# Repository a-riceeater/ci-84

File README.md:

# ci-84: California Instruments 84
An open source, ti-84 equivalent graphing calculator. 

This repository contains CAD files, KiCad project files, and firmware for the calculator.

## Hardware Specifications

- As of 3/5/25, the microcontroller will be a [STM32L471RGT6TR](https://www.digikey.com/en/products/detail/stmicroelectronics/STM32L471RGT6TR/8257935)

- Floating point math

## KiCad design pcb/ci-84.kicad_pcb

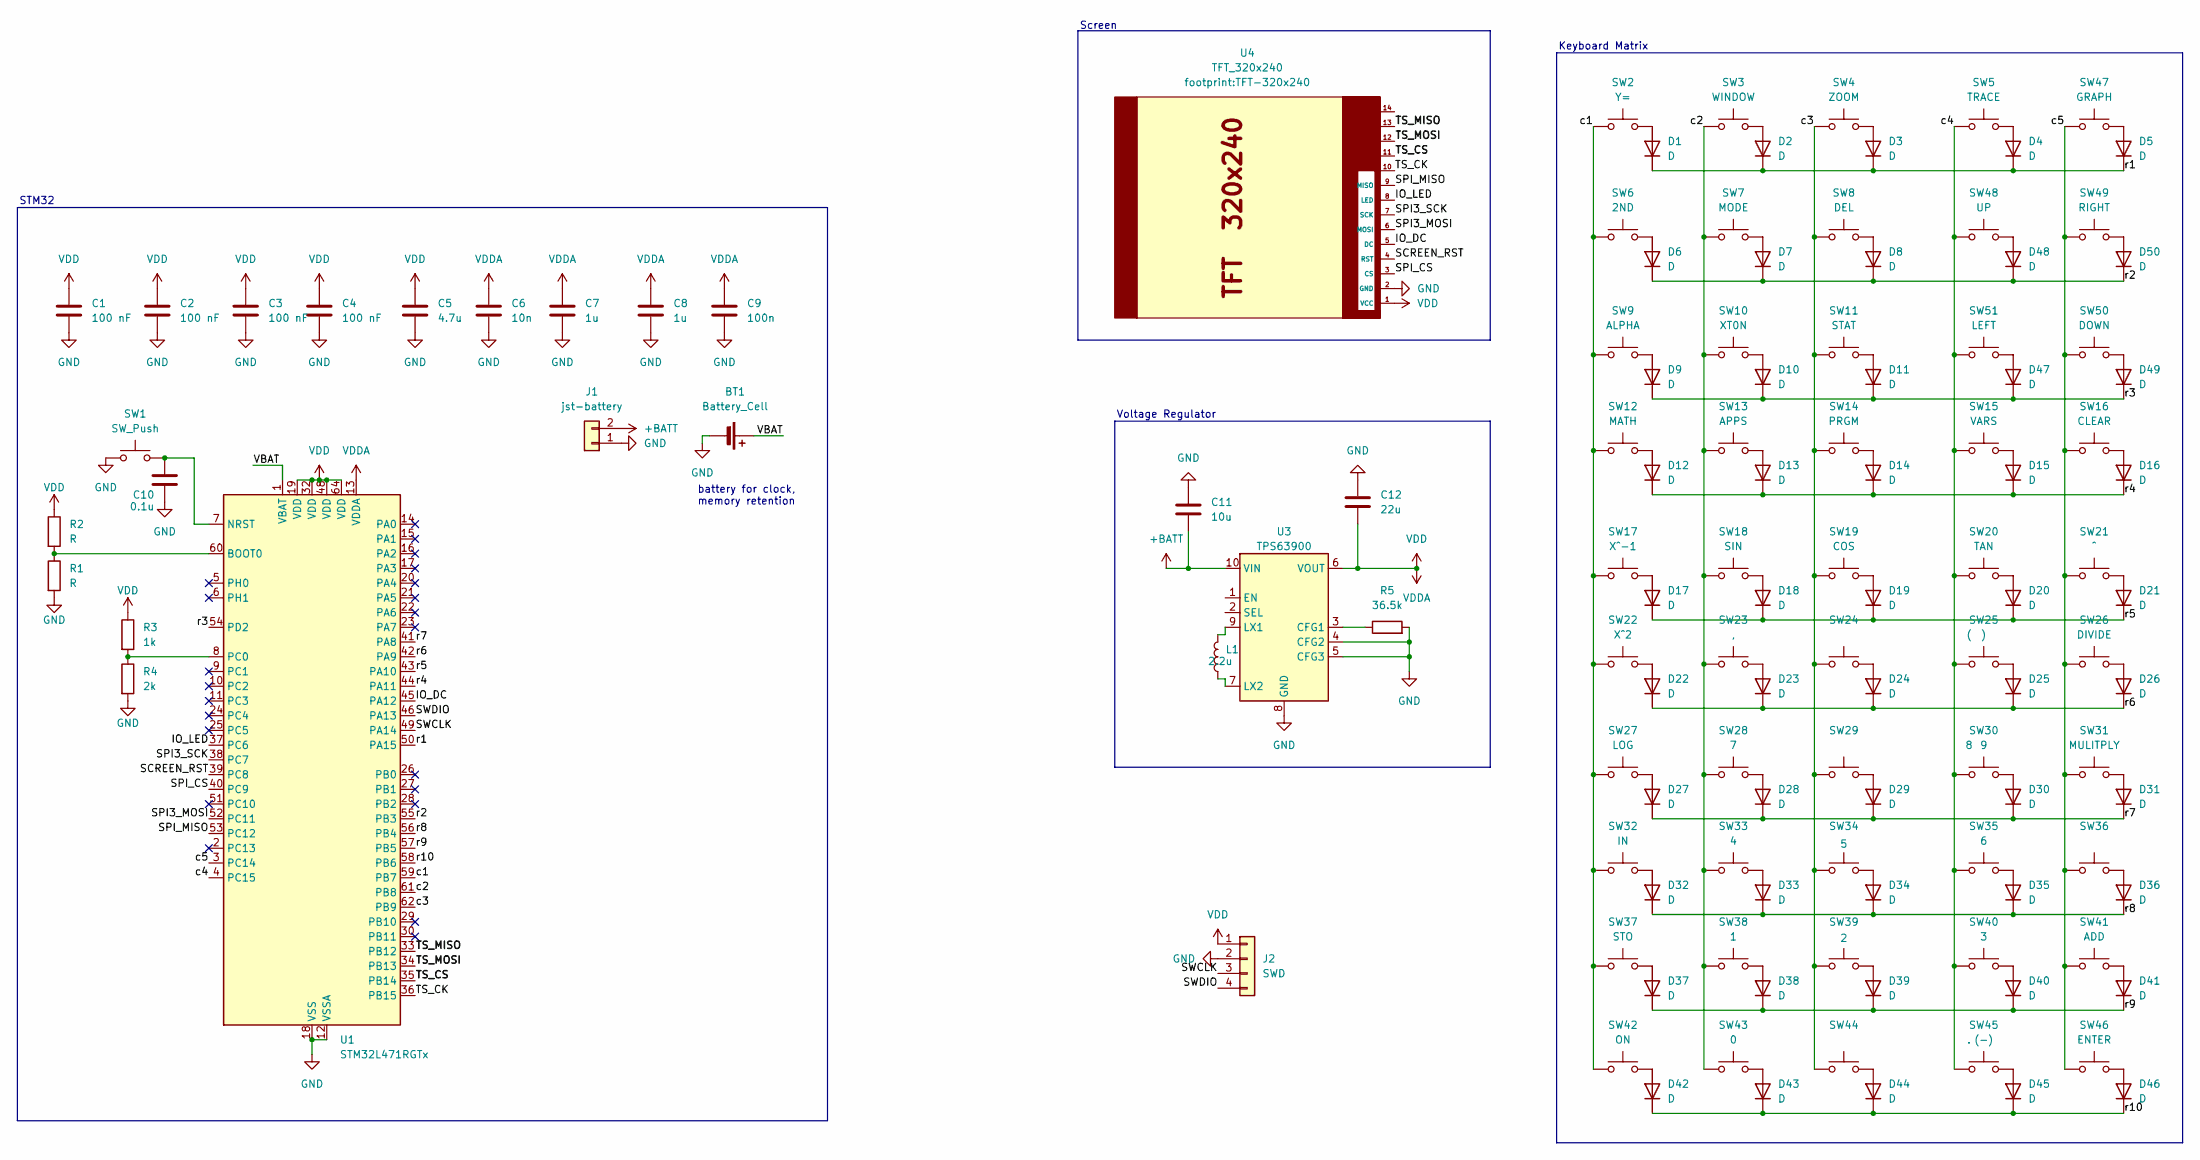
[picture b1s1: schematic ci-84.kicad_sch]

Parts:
BT1: Battery_Cell; BatteryHolder_MPD_BC2003_1x2032
C1, C2, C3, C4: 100 nF; C_0603_1608Metric
C5: 4.7u; C_0603_1608Metric
C6: 10n; C_0603_1608Metric
C7, C8: 1u; C_0603_1608Metric
C9: 100n; C_0603_1608Metric
C10: 0.1u; C_0603_1608Metric
C11: 10u; C_0805_2012Metric
C12: 22u; C_1206_3216Metric
D1, D2, D3, D4, D5, D6, D7, D8, D9, D10, D11, D12, D13, D14, D15, D16, D17, D18, D19, D20, D21, D22, D23, D24, D25, D26, D27, D28, D29, D30, D31, D32, D33, D34, D35, D36, D37, D38, D39, D40, D41, D42, D43, D44, D45, D46, D47, D48, D49, D50: D; D_SOD-123
J1: jst-battery; JST_PH_B2B-PH-K_1x02_P2.00mm_Vertical
J2: SWD; PinHeader_1x04_P2.54mm_Vertical
L1: 2.2u; L_1008_2520Metric
R1, R2: R; R_0603_1608Metric
R3: 1k; R_0603_1608Metric
R4: 2k; R_0603_1608Metric
R5: 36.5k; R_0603_1608Metric
SW1: SW_Push; SW4_1825910-B_TEC
SW2: Y=; SW_Tactile_SPST_NO_Straight_CK_PTS636Sx25SMTRLFS
SW3: WINDOW; SW_Tactile_SPST_NO_Straight_CK_PTS636Sx25SMTRLFS
SW4: ZOOM; SW_Tactile_SPST_NO_Straight_CK_PTS636Sx25SMTRLFS
SW5: TRACE; SW_Tactile_SPST_NO_Straight_CK_PTS636Sx25SMTRLFS
SW6: 2ND; SW_Tactile_SPST_NO_Straight_CK_PTS636Sx25SMTRLFS
SW7: MODE; SW_Tactile_SPST_NO_Straight_CK_PTS636Sx25SMTRLFS
SW8: DEL; SW_Tactile_SPST_NO_Straight_CK_PTS636Sx25SMTRLFS
SW9: ALPHA; SW_Tactile_SPST_NO_Straight_CK_PTS636Sx25SMTRLFS
SW10: XT0N; SW_Tactile_SPST_NO_Straight_CK_PTS636Sx25SMTRLFS
SW11: STAT; SW_Tactile_SPST_NO_Straight_CK_PTS636Sx25SMTRLFS
SW12: MATH; SW_Tactile_SPST_NO_Straight_CK_PTS636Sx25SMTRLFS
SW13: APPS; SW_Tactile_SPST_NO_Straight_CK_PTS636Sx25SMTRLFS
SW14: PRGM; SW_Tactile_SPST_NO_Straight_CK_PTS636Sx25SMTRLFS
SW15: VARS; SW_Tactile_SPST_NO_Straight_CK_PTS636Sx25SMTRLFS
SW16: CLEAR; SW_Tactile_SPST_NO_Straight_CK_PTS636Sx25SMTRLFS
SW17: X^-1; SW_Tactile_SPST_NO_Straight_CK_PTS636Sx25SMTRLFS
SW18: SIN; SW_Tactile_SPST_NO_Straight_CK_PTS636Sx25SMTRLFS
SW19: COS; SW_Tactile_SPST_NO_Straight_CK_PTS636Sx25SMTRLFS
SW20: TAN; SW_Tactile_SPST_NO_Straight_CK_PTS636Sx25SMTRLFS
SW21: ^; SW_Tactile_SPST_NO_Straight_CK_PTS636Sx25SMTRLFS
SW22: X^2; SW_Tactile_SPST_NO_Straight_CK_PTS636Sx25SMTRLFS
SW23: ,; SW_Tactile_SPST_NO_Straight_CK_PTS636Sx25SMTRLFS
SW24: (; SW_Tactile_SPST_NO_Straight_CK_PTS636Sx25SMTRLFS
SW25: ); SW_Tactile_SPST_NO_Straight_CK_PTS636Sx25SMTRLFS
SW26: DIVIDE; SW_Tactile_SPST_NO_Straight_CK_PTS636Sx25SMTRLFS
SW27: LOG; SW_Tactile_SPST_NO_Straight_CK_PTS636Sx25SMTRLFS
SW28: 7; SW_Tactile_SPST_NO_Straight_CK_PTS636Sx25SMTRLFS
SW29: 8; SW_Tactile_SPST_NO_Straight_CK_PTS636Sx25SMTRLFS
SW30: 9; SW_Tactile_SPST_NO_Straight_CK_PTS636Sx25SMTRLFS
SW31: MULITPLY; SW_Tactile_SPST_NO_Straight_CK_PTS636Sx25SMTRLFS
SW32: IN; SW_Tactile_SPST_NO_Straight_CK_PTS636Sx25SMTRLFS
SW33: 4; SW_Tactile_SPST_NO_Straight_CK_PTS636Sx25SMTRLFS
SW34: 5; SW_Tactile_SPST_NO_Straight_CK_PTS636Sx25SMTRLFS
SW35: 6; SW_Tactile_SPST_NO_Straight_CK_PTS636Sx25SMTRLFS
SW36: SUBTRACT; SW_Tactile_SPST_NO_Straight_CK_PTS636Sx25SMTRLFS
SW37: STO; SW_Tactile_SPST_NO_Straight_CK_PTS636Sx25SMTRLFS
SW38: 1; SW_Tactile_SPST_NO_Straight_CK_PTS636Sx25SMTRLFS
SW39: 2; SW_Tactile_SPST_NO_Straight_CK_PTS636Sx25SMTRLFS
SW40: 3; SW_Tactile_SPST_NO_Straight_CK_PTS636Sx25SMTRLFS
SW41: ADD; SW_Tactile_SPST_NO_Straight_CK_PTS636Sx25SMTRLFS
SW42: ON; SW_Tactile_SPST_NO_Straight_CK_PTS636Sx25SMTRLFS
SW43: 0; SW_Tactile_SPST_NO_Straight_CK_PTS636Sx25SMTRLFS
SW44: .; SW_Tactile_SPST_NO_Straight_CK_PTS636Sx25SMTRLFS
SW45: (-); SW_Tactile_SPST_NO_Straight_CK_PTS636Sx25SMTRLFS
SW46: ENTER; SW_Tactile_SPST_NO_Straight_CK_PTS636Sx25SMTRLFS
SW47: GRAPH; SW_Tactile_SPST_NO_Straight_CK_PTS636Sx25SMTRLFS
SW48: UP; SW_Tactile_SPST_NO_Straight_CK_PTS636Sx25SMTRLFS
SW49: RIGHT; SW_Tactile_SPST_NO_Straight_CK_PTS636Sx25SMTRLFS
SW50: DOWN; SW_Tactile_SPST_NO_Straight_CK_PTS636Sx25SMTRLFS
SW51: LEFT; SW_Tactile_SPST_NO_Straight_CK_PTS636Sx25SMTRLFS
U1: STM32L471RGTx; LQFP-64_10x10mm_P0.5mm
U3: TPS63900; WSON-10-1EP_2.5x2.5mm_P0.5mm_EP1.2x2mm_ThermalVias
U4: TFT_320x240; TFT-320x240

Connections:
+BATT: C11.2, J1.2, U3.10 (VIN)
/IO_DC: U1.45 (PA12), U4.5 (DC)
/IO_LED: U1.37 (PC6), U4.8 (LED)
/SCREEN_RST: U1.39 (PC8), U4.4 (RST)
/SPI3_MOSI: U1.52 (PC11), U4.6 (MOSI)
/SPI3_SCK: U1.38 (PC7), U4.7 (SCK)
/SPI_CS: U1.40 (PC9), U4.3 (CS)
/SPI_MISO: U1.53 (PC12), U4.9 (MISO)
/SWCLK: J2.3, U1.49 (PA14)
/SWDIO: J2.4, U1.46 (PA13)
/TS_CK: U1.36 (PB15), U4.10
/TS_CS: U1.35 (PB14), U4.11
/TS_MISO: U1.33 (PB12), U4.13
/TS_MOSI: U1.34 (PB13), U4.12
/VBAT: BT1.1 (+), U1.1 (VBAT)
/c1: SW2.1, SW6.2, SW9.2, SW12.2, SW17.2, SW22.2, SW27.2, SW32.2, SW37.2, SW42.2, U1.59 (PB7)
/c2: SW3.2, SW7.2, SW10.2, SW13.2, SW18.2, SW23.2, SW28.2, SW33.2, SW38.2, SW43.2, U1.61 (PB8)
/c3: SW4.2, SW8.2, SW11.2, SW14.2, SW19.2, SW24.2, SW29.2, SW34.2, SW39.2, SW44.2, U1.62 (PB9)
/c4: SW5.2, SW15.2, SW20.2, SW25.2, SW30.2, SW35.2, SW40.2, SW45.2, SW48.2, SW51.2, U1.4 (PC15)
/c5: SW16.2, SW21.2, SW26.2, SW31.2, SW36.2, SW41.2, SW46.2, SW47.2, SW49.2, SW50.2, U1.3 (PC14)
/r1: D1.1 (K), D2.1 (K), D3.1 (K), D4.1 (K), D5.1 (K), U1.50 (PA15)
/r2: D6.1 (K), D7.1 (K), D8.1 (K), D48.1 (K), D50.1 (K), U1.55 (PB3)
/r3: D9.1 (K), D10.1 (K), D11.1 (K), D47.1 (K), D49.1 (K), U1.54 (PD2)
/r4: D12.1 (K), D13.1 (K), D14.1 (K), D15.1 (K), D16.1 (K), U1.44 (PA11)
/r5: D17.1 (K), D18.1 (K), D19.1 (K), D20.1 (K), D21.1 (K), U1.43 (PA10)
/r6: D22.1 (K), D23.1 (K), D24.1 (K), D25.1 (K), D26.1 (K), U1.42 (PA9)
/r7: D27.1 (K), D28.1 (K), D29.1 (K), D30.1 (K), D31.1 (K), U1.41 (PA8)
/r8: D32.1 (K), D33.1 (K), D34.1 (K), D35.1 (K), D36.1 (K), U1.56 (PB4)
/r9: D37.1 (K), D38.1 (K), D39.1 (K), D40.1 (K), D41.1 (K), U1.57 (PB5)
/r10: D42.1 (K), D43.1 (K), D44.1 (K), D45.1 (K), D46.1 (K), U1.58 (PB6)
GND: BT1.2 (-), C1.2, C2.2, C3.2, C4.2, C5.2, C6.2, C7.2, C8.2, C9.2, C10.2, C11.1, C12.1, J1.1, J2.2, R1.2, R4.2, R5.2, SW1.1, U1.12 (VSSA), U1.18 (VSS), U1.31 (VSS), U1.47 (VSS), U1.63 (VSS), U3.4 (CFG2), U3.5 (CFG3), U3.8 (GND), U3.11 (GND), U4.2 (GND)
unnamed: D1.2 (A), SW2.2
unnamed: D2.2 (A), SW3.1
unnamed: D3.2 (A), SW4.1
unnamed: D4.2 (A), SW5.1
unnamed: D5.2 (A), SW47.1
unnamed: D6.2 (A), SW6.1
unnamed: D7.2 (A), SW7.1
unnamed: D8.2 (A), SW8.1
unnamed: D9.2 (A), SW9.1
unnamed: D10.2 (A), SW10.1
unnamed: D11.2 (A), SW11.1
unnamed: D12.2 (A), SW12.1
unnamed: D13.2 (A), SW13.1
unnamed: D14.2 (A), SW14.1
unnamed: D15.2 (A), SW15.1
unnamed: D16.2 (A), SW16.1
unnamed: D17.2 (A), SW17.1
unnamed: D18.2 (A), SW18.1
unnamed: D19.2 (A), SW19.1
unnamed: D20.2 (A), SW20.1
unnamed: D21.2 (A), SW21.1
unnamed: D22.2 (A), SW22.1
unnamed: D23.2 (A), SW23.1
unnamed: D24.2 (A), SW24.1
unnamed: D25.2 (A), SW25.1
unnamed: D26.2 (A), SW26.1
unnamed: D27.2 (A), SW27.1
unnamed: D28.2 (A), SW28.1
unnamed: D29.2 (A), SW29.1
unnamed: D30.2 (A), SW30.1
unnamed: D31.2 (A), SW31.1
unnamed: D32.2 (A), SW32.1
unnamed: D33.2 (A), SW33.1
unnamed: D34.2 (A), SW34.1
unnamed: D35.2 (A), SW35.1
unnamed: D36.2 (A), SW36.1
unnamed: D37.2 (A), SW37.1
unnamed: D38.2 (A), SW38.1
unnamed: D39.2 (A), SW39.1
unnamed: D40.2 (A), SW40.1
unnamed: D41.2 (A), SW41.1
unnamed: D42.2 (A), SW42.1
unnamed: D43.2 (A), SW43.1
unnamed: D44.2 (A), SW44.1
unnamed: D45.2 (A), SW45.1
unnamed: D46.2 (A), SW46.1
unnamed: D47.2 (A), SW51.1
unnamed: D48.2 (A), SW48.1
unnamed: D49.2 (A), SW50.1
unnamed: D50.2 (A), SW49.1
unnamed: R1.1, R2.2, U1.60 (BOOT0)
unnamed: C10.1, SW1.2, U1.7 (NRST)
unnamed: R3.2, R4.1, U1.8 (PC0)
unnamed: R5.1, U3.3 (CFG1)
unnamed: L1.2, U3.9 (LX1)
unnamed: L1.1, U3.7 (LX2)
VDD: C1.1, C2.1, C3.1, C4.1, C5.1, C6.1, C7.1, C8.1, C9.1, C12.2, J2.1, R2.1, R3.1, U1.13 (VDDA), U1.19 (VDD), U1.32 (VDD), U1.48 (VDD), U1.64 (VDD), U3.6 (VOUT), U4.1 (VCC)

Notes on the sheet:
Keyboard Matrix
T_IRQ
Voltage Regulator
Screen
battery for clock, memory retention
T_DO
T_DIN
STM32
T_CLK
T_CS

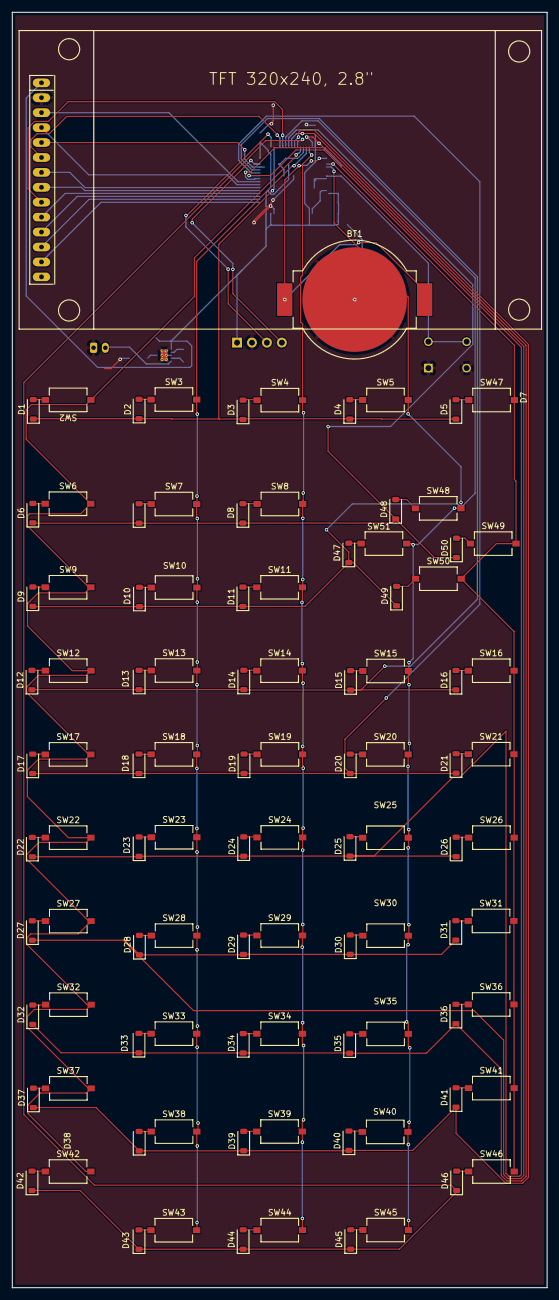
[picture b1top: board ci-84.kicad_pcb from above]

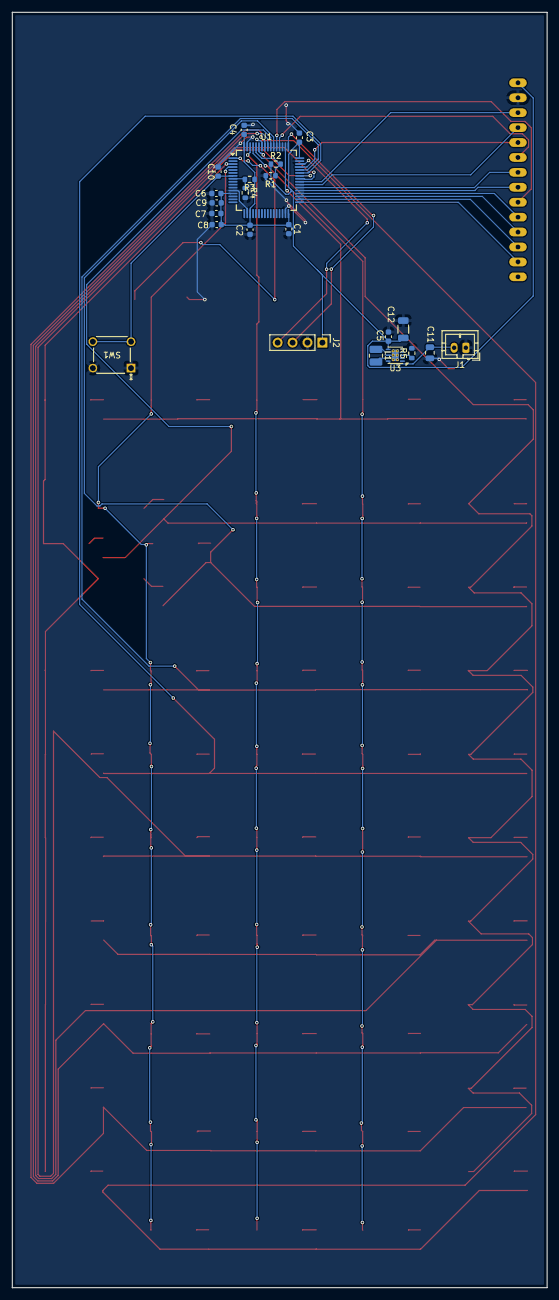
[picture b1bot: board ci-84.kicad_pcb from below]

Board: 2 copper layers, 91.0 x 217.0 mm, 125 parts (23 on the bottom side), 88 nets.

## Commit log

2025-03-05 readme
2025-03-05 kicad
2025-03-05 microcon troller
2025-03-05 add link
2025-03-08 stm32 power, data, screen
2025-03-09 keyboard matrix
2025-03-10 add diode matrix, start
2025-03-10 finish keyboard diode matrix
2025-03-12 finish some stuff idk
2025-03-12 more keyboarD
2025-03-12 add missing outline rows
2025-03-12 finish keyboard matrix
2025-03-12 finish wiring matrix
2025-03-12 update outline, add arrow keys
2025-03-12 add correct spaing
2025-03-12 fix missing connections
2025-03-13 move arrow keys to keyboard matrix, add labels for riows
2025-03-13 wire matrix to mcirocontroller
2025-03-13 finish matrix connections
2025-03-13 finish wiring everthing
2025-03-17 sheets for schematic
2025-03-20 sw pins
2025-03-25 more stuff
2025-04-02 stuff
2025-04-02 cleaned schematic and added final components
2025-04-03 finish all connections
2025-04-03 save
